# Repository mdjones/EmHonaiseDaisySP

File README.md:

# EmHonaise DaisySP

## Purpose

A place to support DaisySP development.

This is an excellent intro to the platform: GPIO, serial printing, ADC
[libDaisy ref docs](https://electro-smith.github.io/libDaisy/index.html)

## Setup

How to setup your enviornment for DaisySP dev.

See [DaisyWiki](https://github.com/electro-smith/DaisyWiki/wiki/1.-Setting-Up-Your-Development-Environment) for setting up your development
enviornment.

* Build the DaisySP submodules

```bash
make
```

* Install the toolchain tools

The tool chain are build 
[utilities](https://github.com/electro-smith/DaisyWiki/wiki/Understanding-the-Toolchain) 
needed for DaisySP dev. You are likely to have a few of them already. 
Electrosmith also provides utilities to install them for you.

* Create your module

Boards: patch_sm,seed

```bash
./helper.py create ./projects/MyDSPProj --board patch_sm
```

## Build

For each example directory do the following after 
[Flashing](https://github.com/electro-smith/DaisyWiki/wiki/1.-Setting-Up-Your-Development-Environment#4-Run-the-Blink-Example)
the Daisy via USB.

```bash
make clean ; make ; make program-dfu
```

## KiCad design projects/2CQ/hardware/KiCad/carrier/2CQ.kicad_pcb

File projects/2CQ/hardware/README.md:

# Notes for Hardware

The OLED needs a switching power supply (The Patch-SM already has one). I am
using the same OLED as the [Electrosmith Patch](https://electro-smith.com/products/patch)
with [schematic](https://daisy.nyc3.cdn.digitaloceanspaces.com/products/patch/ES_Daisy_Patch_Rev4.pdf)

## OLED Pin Layout

This is my OLED: [SSD1306 for 51 STM32 Arduino](https://www.amazon.com/dp/B01N1LZQA8?th=1) [or](http://hiletgo.com/ProductDetail/2169510.html)

KiCad Ref[https://kicad.github.io/footprints/Display.html]

[PCB](https://github.com/adafruit/Adafruit-128x64-Monochrome-OLED-PCB)

[Footprint](https://kicadrookie.blogspot.com/2022/01/096-inch-128x64-spi-display-module_4.html) - look for the link at near the bottom of follow the instructions. I could not find the datasheet diagram the designer keeps keeps showing. 

Put the 128x64_0.96_Disp_Module.kicad_mod file in side a .pretty folder

```txt
HiLetgo 0.96" inch SPI Serial 128 * 64
12864 Characters OLED LCD Display 
SSD1306 for 51 STM32 Arduino Font Color White 
```

Did a bunch of failing research, Discord, Forum, code reading. Finally decided
to search for path_sm and `OledDisplay<SSD130x4WireSpi128x64Driver>` on github
and found <https://github.com/electro-smith/libDaisy/blob/master/examples/OLED_SPI/OledSPI.cpp>

[PINS](https://electronics.stackexchange.com/questions/581256/wiring-a-ssd1306-oled-with-spi)

Final Pin set up is:

| OLED Pin Name | patch_sm pin | function |
| ------------- | ------------ | -------- |
| GND           | A7           | GND      |
| VCC           | A10          | +3V3     |
| D0            | D10          | SCLK     |
| D1            | D9           | MOSI     |
| RES           | D3           | RESET    |
| DC            | D2           | dc       |
| CS            | Not Wired    |          |

Correction: Based on <https://forum.electro-smith.com/t/connecting-an-oled-to-the-patch-init/7501/2>

> note! I am using +3V3 instead of +5V5 as above.

TODO: I feel like A3 and A2 should be swapped 

| OLED Pin Name | patch_sm pin | function    | P1-M12 patch.Init() breakout | Wire color |
| ------------- | ------------ | ----------- | ---------------------------- | ---------- |
| GND           | A4           | GND         | 12                           | black      |
| VCC           | A10          | +3V3 (+5V)  | 1                            | white      |
| D0            | D10          | SCLK        | 7                            | grey       |
| D1            | D9           | MOSI  (SDA) | 5                            | purple     |
| RES           | A3           | RESET       | 10                           | blue       |
| DC            | A2           | dc          | 9                            | green      |
| CS            | Not Wired    | Chip Select | Not wired*                   | Not wired  |

In the Daisy Patch OLED_CS is wired to 8*2 (GPIO8(SPI1_NSS)) 

## 3 Way Switch

<https://forum.electro-smith.com/t/adding-a-3-way-switch-to-seed/2418/4>

## Panels

<https://forum.electro-smith.com/t/frequently-asked-questions-specifically-about-patch-init/2630/5>

## Using the Audio outs as CV outs

<https://forum.electro-smith.com/t/audio-outputs-negate-the-value-i-send-from-firmware/3566/8>

## Knobs

These are probably the knobs. 

<https://www.thonk.co.uk/shop/make-noise-mutable-style-knobs/>

## Jacks

Thonkin jacks <https://www.thonk.co.uk/wp-content/uploads/2014/02/Thonkiconn_Jack_Datasheet.pdf>

1: The long leg in front connects to the brushing/sleave?
2: Normally connects to 3. I thought this would be useful but seems useless here.
3: Normally connects to 2. Connects to cable plug when norm is broken.

2 and 3 are normally connected
If you plug something in 3 will output the voltage

I am not sure this is correct but it works.

1: Connect to gate_patched pin. This only works if the cable is also plugged
into a grounded source.
2: Connect to ground. Don't think this is doing anything.
3: Connect to gate in 

## Trouble shooting

Problem: CV values hoover around 1. Make sure the 12V power supply is on

## TODOs

TODO: Consider using project libs for sharing <https://forum.kicad.info/t/creating-a-project-using-global-libraries-and-then-exporting-to-local-libraries/47132/3>
TODO: Consider using SD_D2 for Gate 1 in patch switch
TODO: Consider swapping SIG_UART_TX and SIG_UART_RX
TODO: Test channel 2
TODO: Test all switches
TODO: Can I/should I change the patch labels to be more informative for this
project?
TODO: Put no connect flags

## KCad

<https://github.com/labtroll/KiCad-DesignRules>

Excellent video series. 

<https://youtu.be/vLnu21fS22s?si=ND8ia9d4luT5V4JJ>

## Pin optimization

Some of the pins I chose where so I could test them out on the patch.Init() 
break out board. But they are awkwardly named. But it will make prototyping easier

TODO: Why am I using SIG_SPI_NSS for Gate 1 patched? I could use SD_D2? I used it because I could check on the patch init? 

<https://github.com/sethhillbrand/kicad_templates>

Imported PCB settings from <https://github.com/sethhillbrand/kicad_templates/tree/master/JLCPCB_1-2Layer>

## Edge cuts

patch.Init() is 111.0 mm x 48.5 mm

## Models

[Thonkiconn](https://grabcad.com/library/wqp-pj398sm-1)

I didn't keep track of all the models but I pulled some from 
<https://grabcad.com/> and some from <https://www.digikey.com>.

These connectors might be able to be used for connecting the display

<https://www.mouser.com/ProductDetail/Preci-dip/801-87-050-10-001101?qs=FtMuP6KVi2S5kFH%252BuHX1%252Bw%3D%3D>
These standoffs should work
<https://www.mouser.com/ProductDetail/Wurth-Elektronik/971070244?qs=%252BEew9%252B0nqrAahtXL2o5lAw%3D%3D>

## EU Format

3U = 128.5 mm

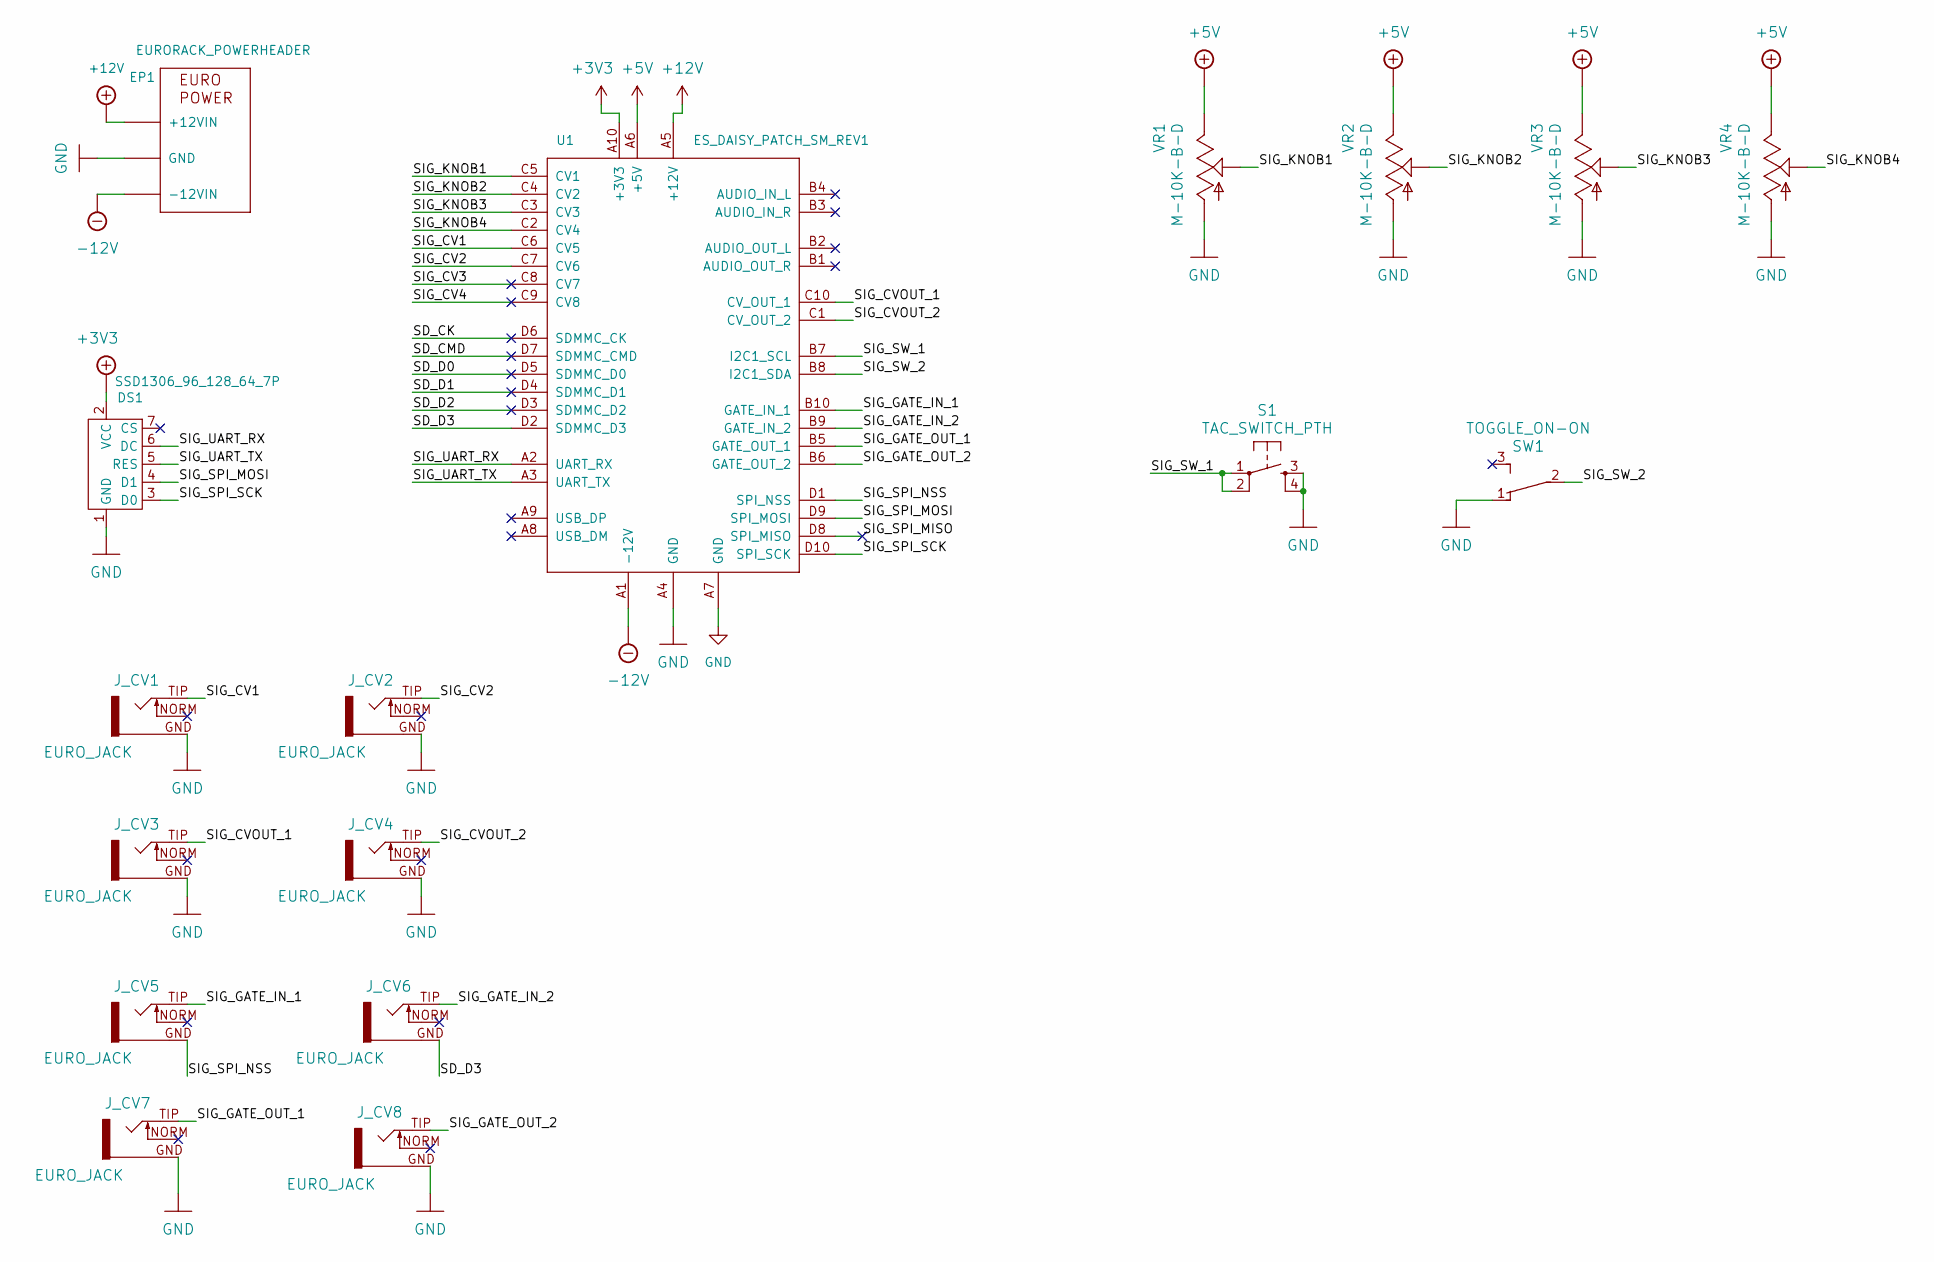
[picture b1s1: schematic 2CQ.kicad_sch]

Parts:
DS1: SSD1306_96_128_64_7P; 128x64_0.96_Disp_Module
EP1: EURORACK_POWERHEADER; EURORACK_POWER_SHROUD_LOCK
J_CV1, J_CV2, J_CV3, J_CV4, J_CV5, J_CV6, J_CV7, J_CV8: EURO_JACK; S_JACK
S1: TAC_SWITCH_PTH; TL1105SPF250Q_SILK
SW1: TOGGLE_ON-ON
U1: ES_DAISY_PATCH_SM_REV1
VR1, VR2, VR3, VR4: M-10K-B-D; 9MM_SNAP-IN_POT_SILK

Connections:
+3V3: DS1.2 (VCC), U1.A10 (+3V3)
+5V: U1.A6 (+5V), VR1.3, VR2.3, VR3.3, VR4.3
+12V: EP1.+12V0 (+12VIN), EP1.+12V1 (+12VIN), U1.A5 (+12V)
-12V: EP1.-12V0 (-12VIN), EP1.-12V1 (-12VIN), U1.A1 (-12V)
/SD_CK: U1.D6 (SDMMC_CK)
/SD_CMD: U1.D7 (SDMMC_CMD)
/SD_D0: U1.D5 (SDMMC_D0)
/SD_D1: U1.D4 (SDMMC_D1)
/SD_D2: U1.D3 (SDMMC_D2)
/SD_D3: J_CV6.GND, U1.D2 (SDMMC_D3)
/SIG_CV1: J_CV1.TIP, U1.C6 (CV5)
/SIG_CV2: J_CV2.TIP, U1.C7 (CV6)
/SIG_CV3: U1.C8 (CV7)
/SIG_CV4: U1.C9 (CV8)
/SIG_CVOUT_1: J_CV3.TIP, U1.C10 (CV_OUT_1)
/SIG_CVOUT_2: J_CV4.TIP, U1.C1 (CV_OUT_2)
/SIG_GATE_IN_1: J_CV5.TIP, U1.B10 (GATE_IN_1)
/SIG_GATE_IN_2: J_CV6.TIP, U1.B9 (GATE_IN_2)
/SIG_GATE_OUT_1: J_CV7.TIP, U1.B5 (GATE_OUT_1)
/SIG_GATE_OUT_2: J_CV8.TIP, U1.B6 (GATE_OUT_2)
/SIG_KNOB1: U1.C5 (CV1), VR1.2
/SIG_KNOB2: U1.C4 (CV2), VR2.2
/SIG_KNOB3: U1.C3 (CV3), VR3.2
/SIG_KNOB4: U1.C2 (CV4), VR4.2
/SIG_SPI_MISO: U1.D8 (SPI_MISO)
/SIG_SPI_MOSI: DS1.4 (D1), U1.D9 (SPI_MOSI)
/SIG_SPI_NSS: J_CV5.GND, U1.D1 (SPI_NSS)
/SIG_SPI_SCK: DS1.3 (D0), U1.D10 (SPI_SCK)
/SIG_SW_1: S1.1, S1.2, U1.B7 (I2C1_SCL)
/SIG_SW_2: SW1.2, U1.B8 (I2C1_SDA)
/SIG_UART_RX: DS1.6 (DC), U1.A2 (UART_RX)
/SIG_UART_TX: DS1.5 (RES), U1.A3 (UART_TX)
GND: DS1.1 (GND), EP1.GND0 (GND), EP1.GND1 (GND), EP1.GND2 (GND), EP1.GND3 (GND), EP1.GND4 (GND), EP1.GND5 (GND), J_CV1.GND, J_CV2.GND, J_CV3.GND, J_CV4.GND, J_CV7.GND, J_CV8.GND, S1.3, S1.4, SW1.1 (O), U1.A4 (GND), U1.A7 (GND), VR1.1, VR2.1, VR3.1, VR4.1

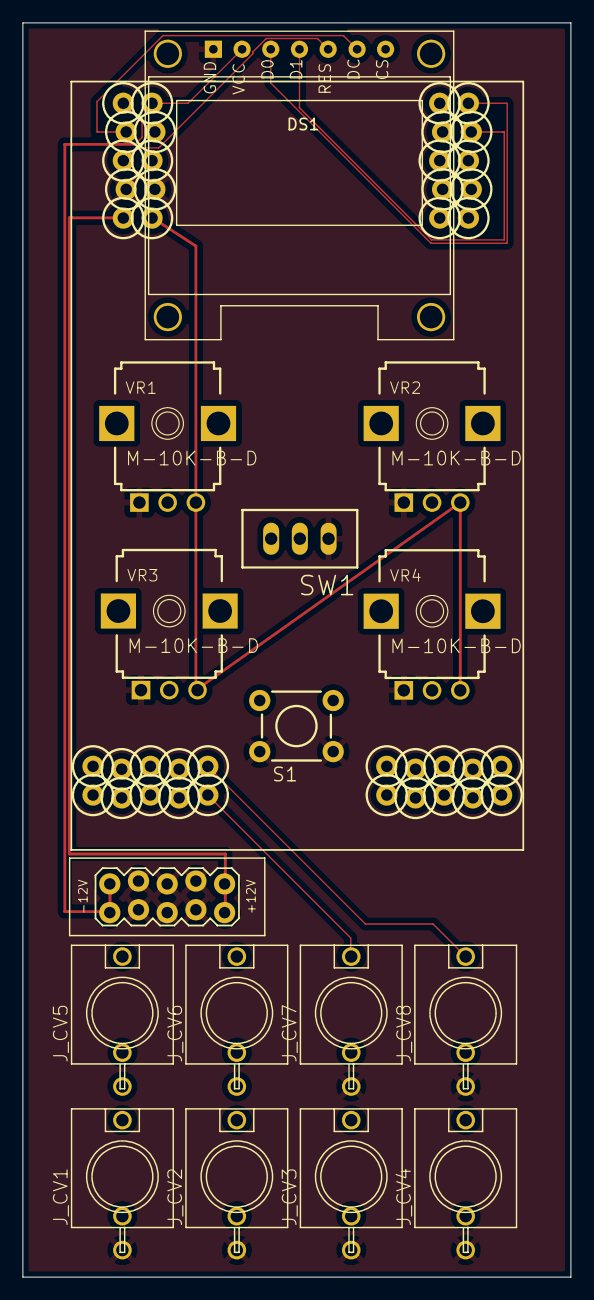
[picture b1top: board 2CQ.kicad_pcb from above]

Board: 2 copper layers, 48.5 x 111.0 mm, 17 parts (0 on the bottom side), 25 nets.

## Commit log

2024-02-04 word
2024-02-04 Note on how to buil
2024-02-04 Reverb
2024-02-04 Stuff for templates
2024-02-04 Connect swith to hw LED
2024-02-04 Added blink example and more docs
2024-02-04 README
2024-02-04 Added AudioCallback
2024-02-04 Comment
2024-02-04 Just somde code to test ot basic libDaisy stuff
2024-02-04 REverb works but its noisy
2024-02-04 Test adc.GetFloat()
2024-02-04 Simplified template
2024-02-04 Print a readout of switch state
2024-02-04 Have a fload for intensity
2024-02-04 Added submods + README
2024-02-04 Format
2024-02-04 helper.py copied from https://github.com/electro-smith/DaisyExamples
2024-02-04 Formatting
2024-02-04 README stuff
2024-02-04 README comment
2024-02-04 Start SimpleTouchQuantize
2024-02-04 Trying to read a knob
2024-02-04 Remove .gitmodule
2024-02-04 Added submods
2024-02-04 Some minor stuff
2024-02-04 Moved Blink
2024-02-04 Removed simple touch examples
2024-02-04 Added Interphase project
2024-04-27 Fixed loc of libDaisy
2024-04-27 First commit of InitQuant
2024-04-27 Replaced LENGHTOF with sizeof
2024-04-27 Got ADC IO mostly working
2024-04-27 Added WriteCvOut
2024-04-27 Comment some stuff out
2024-04-28 Adde some logging
2024-04-29 Got basic logging and IO working
2024-04-29 Send voltage to CV Out
2024-04-30 Got basic voltage to scale/root working More logging
2024-05-03 Add debug flag
2024-05-03 Got trigger working ... kind've
2024-05-04 Added octave shift and improved triggering on note change
2024-05-04 Added a blink on param change
2024-05-04 Reduce octave shift
2024-11-22 Adedd operations instructions to README
2024-11-22 Bullet points
2024-11-22 Added Makefile to root dir
2024-11-22 Typo
2024-11-22 Typos
2024-11-22 First commit for sidekcik
2024-11-22 Copied main.cpp and removed MIDI stuff
2024-12-23 Note in README
2024-12-23 Init 2CQSandBox
2024-12-23 Rename 2CQ
2024-12-23 Move
2024-12-23 Added two gate switches
2024-12-23 Adeded debug indicator
2024-12-23 Build instauctoins
2024-12-24 Added some values and ability to select the edit channel
2024-12-24 Set values for the two channels.
    Certain values are only set on the selected edited channel
2024-12-24 process out_voct
2024-12-24 Send quantized value to output
2024-12-24 Move rescale
2024-12-24 set voct to channel
2024-12-24 Fixed bug with undefined out channels
2024-12-25 Adde quant_voct to channel and estimated when gate and quant_voct assignments should be executed
2024-12-26 First pass at moving the channel data to a class
    Currently getting undefined reference messages post compile
2024-12-26 First imple of Channel Class
2024-12-26 Removed static
2024-12-26 Added output voct accessor
2024-12-26 Chamged member names differently then init names
2024-12-26 C++ needs to be passed with a '&' in order for the object to be edited
2024-12-26 pointers are a pain
2024-12-26 Removed rescaling of input voltage And removed debug lines
2024-12-26 Cleanup
2024-12-26 Process channel 2 too
2024-12-26 Removed inapropriate CvOut call
2024-12-27 Renamed some vars
2024-12-27 Scale ADC input to 0-5 volts
2024-12-27 Renamed volts to adc
2025-01-02 Hard code gate_patched for now
2025-01-02 Added some notes
2025-01-02 Formating
2025-01-03 Some OLED testing
2025-01-03 Trying to config the OLED
2025-01-03 Removed comment
2025-01-04 Got OLED Test to work
2025-01-04 Notes for OLED HW
2025-01-04 Cleaned up README
2025-01-04 Delagate Display to two_cq_hw.cpp
2025-01-04 Added in an UpdateOled method
2025-01-04 Reset the string buffer
2025-01-04 msg changes
2025-01-05 Use channel to store the current values for comparison
2025-01-05 Moved channel to two_cq_hw.cpp
2025-01-05 Removed unused includes
2025-01-05 Added some constants for IO
2025-01-05 Impl
    * Channel switch: Select which channel is selected for setting adjustment. A
    setting will be changed only if a knob has been adjusted or the All button
    has been triggered.
2025-01-05 Turn off debug
2025-01-11 Added in new config based on
    https://forum.electro-smith.com/t/connecting-an-oled-to-the-patch-init/7501
2025-01-11 Fixed some pins
2025-01-11 Display msg
2025-01-11 Fixed a wrong setting to out
2025-01-12 removed print lines and made a comment
2025-01-12 Mirror CV OUTs in Audio Outs
2025-01-12 Update OLED properly on startup
2025-01-12 Added channel reset
2025-01-12 Make sure Audio out CV is maxed at 5 volts
2025-01-12 CLeaned up OLED code a bit
2025-01-12 Added accessor for sparcity
2025-01-12 Added splash
2025-01-12 SHorted splash
2025-01-12 Implemented sparcity array mask
2025-01-12 Turned off logging
2025-01-13 Use indicate to indicate a quantitation event
2025-01-13 Added new mask and re-ordered mask order
2025-01-13 Change sparcity to mask
2025-01-13 Some more renaming to mask
2025-01-13 Let user know when a mask is not being applied
2025-01-13 Added THIRD_FIFTH_SEVENTH_MASK
2025-01-14 Comments
2025-01-16 Fixed bug with channel not chaning on OLED. May have also fixed an screen scramble bug. We will see.
2025-01-16 Added THIRD_FIFTH_SIXTH
2025-01-16 Added note on knobs
2025-01-17 OLED + header file
2025-01-17 Created a two_cq_hw.h
2025-01-18 Got rid of quant event indicator and added gate in indicator
2025-01-19 Got gate in to work
2025-01-19 Use PathchSM CV pin names
2025-01-20 Added kiCad project
2025-01-20 Added patch_sm to schematic
2025-01-21 KiCad Schematic
2025-01-21 Added footprints and some labels
2025-01-22 Started PCB
2025-01-24 Restart PCB
2025-01-24 Use project footprint for 128x64_0.96_Disp_Module
2025-01-24 Upgrade to KiCad 8.0
2025-01-24 Hard code patch for now Add Yo Scale
2025-01-24 Fxed chanel desg
2025-01-25 Added dru and OLED footprint
2025-01-25 A bunch of symbol and footprint optimizations
2025-01-25 Added ES_Daisy_Patch_SM_FB_Rev1-eagle-import.kicad_sym
2025-01-25 Some electrical check stuff
2025-01-25 Not really sure
2025-01-26 Added pin names to DSP footpring
2025-01-26 .gitignore
2025-01-26 Imported PCB settings from https://github.com/sethhillbrand/kicad_templates/tree/master/JLCPCB_1-2Layer
2025-01-28 Fixed power warnings
2025-01-28 Added hard coded labels
2025-01-28 Notes on edge cuts
2025-02-01 Fixed some errors with misnamed pins in the footprint
2025-02-01 Added model to thonk jack
2025-02-01 Added 3d models and updated PCB
2025-02-01 moved power
2025-02-03 PCB Stuff
2025-02-03 Moving shit around
2025-02-05 Added some models
2025-02-05 Moved cariar KiCad project
2025-03-15 Added PENTATONIC_MASK
2025-03-16 Added KiCad/panel/2CQPanel.kicad_pro
2025-03-16 Added some wires
2025-03-20 routing organizing

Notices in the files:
projects/2CQ/hardware/2CQ/2CQ.kicad_sch:
MIT License
